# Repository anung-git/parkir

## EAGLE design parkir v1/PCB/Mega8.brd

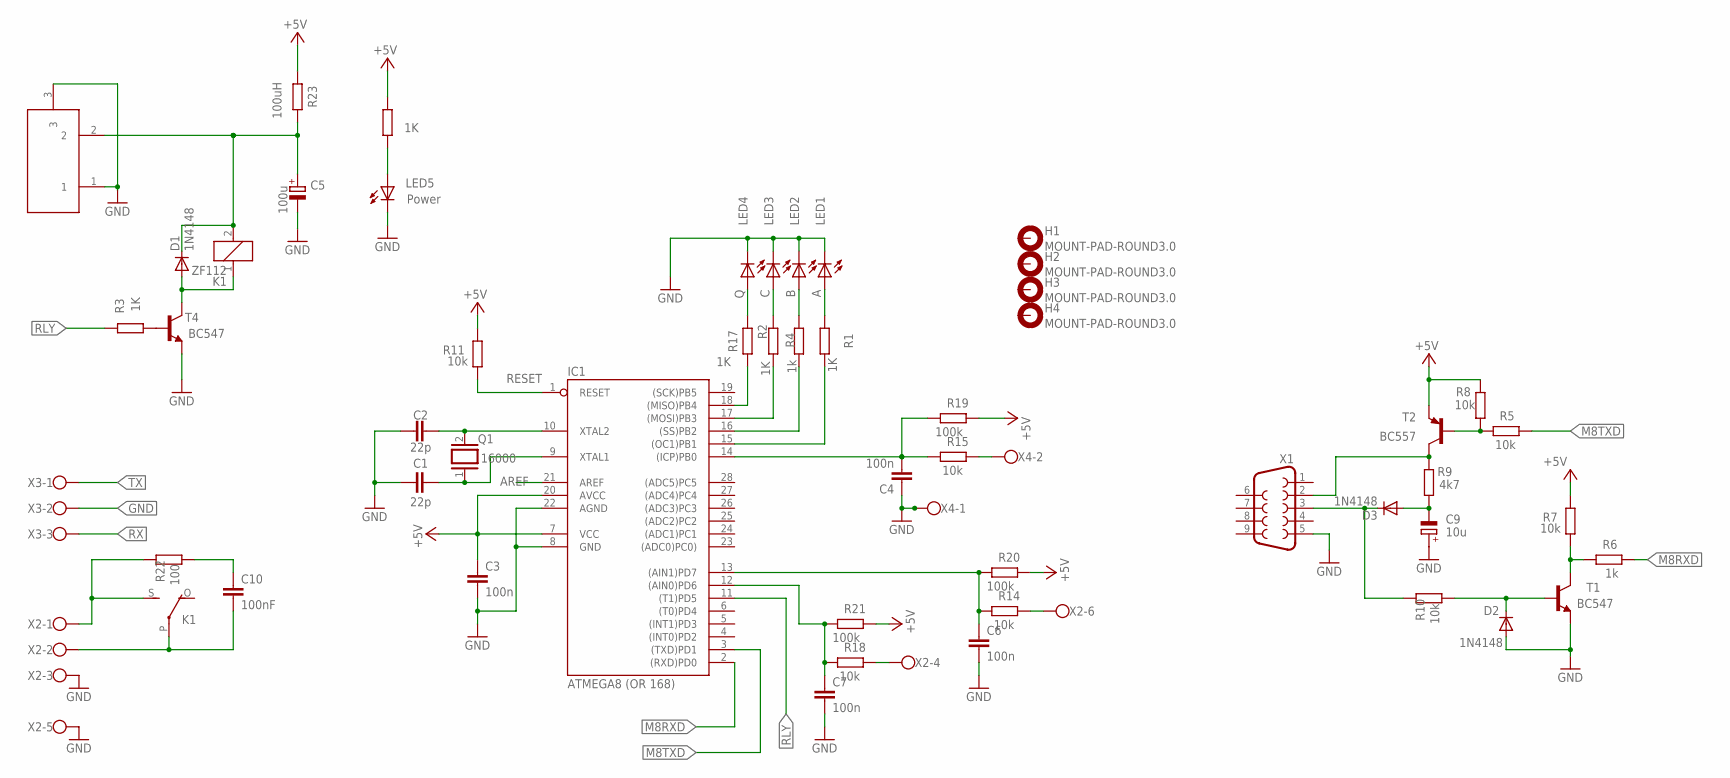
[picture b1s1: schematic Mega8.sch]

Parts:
C1, C2: 22p; C050-025X075
C3, C4, C6, C7: 100n; C050-025X075
C5: 100u; E3,5-8
C9: 10u; E5-6
C10: 100nF; C102-043X133
D1, D2, D3: 1N4148; DO35-10
DC1: DC21MMX; DC-21MM
H1, H2, H3, H4: MOUNT-PAD-ROUND3.0; 3,0-PAD
IC1: ATMEGA8 (OR 168); DIL28-3
K1: ZF112
LED1: A; LED3MM
LED2: B; LED3MM
LED3: C; LED3MM
LED4: Q; LED3MM
LED5: Power; LED3MM
Q1: 16000; Q
R1, R2, R3, R16, R17: 1K; 0207/10
R4, R6: 1k; 0207/10
R5, R7, R8, R10, R11, R14, R15, R18: 10k; 0207/10
R9: 4k7; 0207/10
R19, R20, R21: 100k; 0207/10
R22: 100; 0207/10
R23: 100uH; 0207/10
T1, T4: BC547; TO92
T2: BC557; TO92-EBC
X1: F09H
X2: W237-6
X3: W237-103
X4: W237-102

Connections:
+5V: C3.1, IC1.7 (VCC), IC1.20 (AVCC), R7.2, R8.1, R11.2, R16.2, R19.1, R20.1, R21.1, R23.2, T2.E
AREF: IC1.21 (AREF)
GND: C1.1, C2.1, C3.2, C4.1, C5.-, C6.2, C7.2, C9.+, D2.A, DC1.1, DC1.3, IC1.8 (GND), IC1.22 (AGND), LED1.K (C), LED2.K (C), LED3.K (C), LED4.K (C), LED5.K (C), T1.1 (E), T4.1 (E), X1.5, X2.3, X2.5, X3.2, X4.1
M8RXD: IC1.2 ((RXD)PD0), R6.1
M8TXD: IC1.3 ((TXD)PD1), R5.1
unnamed: R3.1, T4.2 (B)
unnamed: C9.-, D3.A, R9.1
unnamed: LED2.A, R4.1
unnamed: D1.A, K1.1, T4.3 (C)
unnamed: R18.1, X2.4
unnamed: C1.2, IC1.9 (XTAL1), Q1.1
unnamed: C2.2, IC1.10 (XTAL2), Q1.2
unnamed: K1.S, R22.2, X2.1
unnamed: C10.2, K1.P, X2.2
unnamed: C4.2, IC1.14 ((ICP)PB0), R15.2, R19.2
unnamed: C6.1, IC1.13 ((AIN1)PD7), R14.2, R20.2
unnamed: R14.1, X2.6
unnamed: IC1.15 ((OC1)PB1), R1.2
unnamed: IC1.16 ((SS)PB2), R4.2
unnamed: IC1.17 ((MOSI)PB3), R2.2
unnamed: LED5.A, R16.1
unnamed: C7.1, IC1.12 ((AIN0)PD6), R18.2, R21.2
unnamed: LED4.A, R17.1
unnamed: IC1.18 ((MISO)PB4), R17.2
unnamed: R15.1, X4.2
unnamed: R6.2, R7.1, T1.3 (C)
unnamed: R5.2, R8.2, T2.B
unnamed: C10.1, R22.1
unnamed: D2.C, R10.1, T1.2 (B)
unnamed: C5.+, D1.C, DC1.2, K1.2, R23.1
unnamed: LED3.A, R2.1
unnamed: LED1.A, R1.1
RESET: IC1.1 (RESET), R11.1
RLY: IC1.11 ((T1)PD5), R3.2
RX: D3.C, R10.2, X1.3, X3.3
TX: R9.2, T2.C, X1.2, X3.1

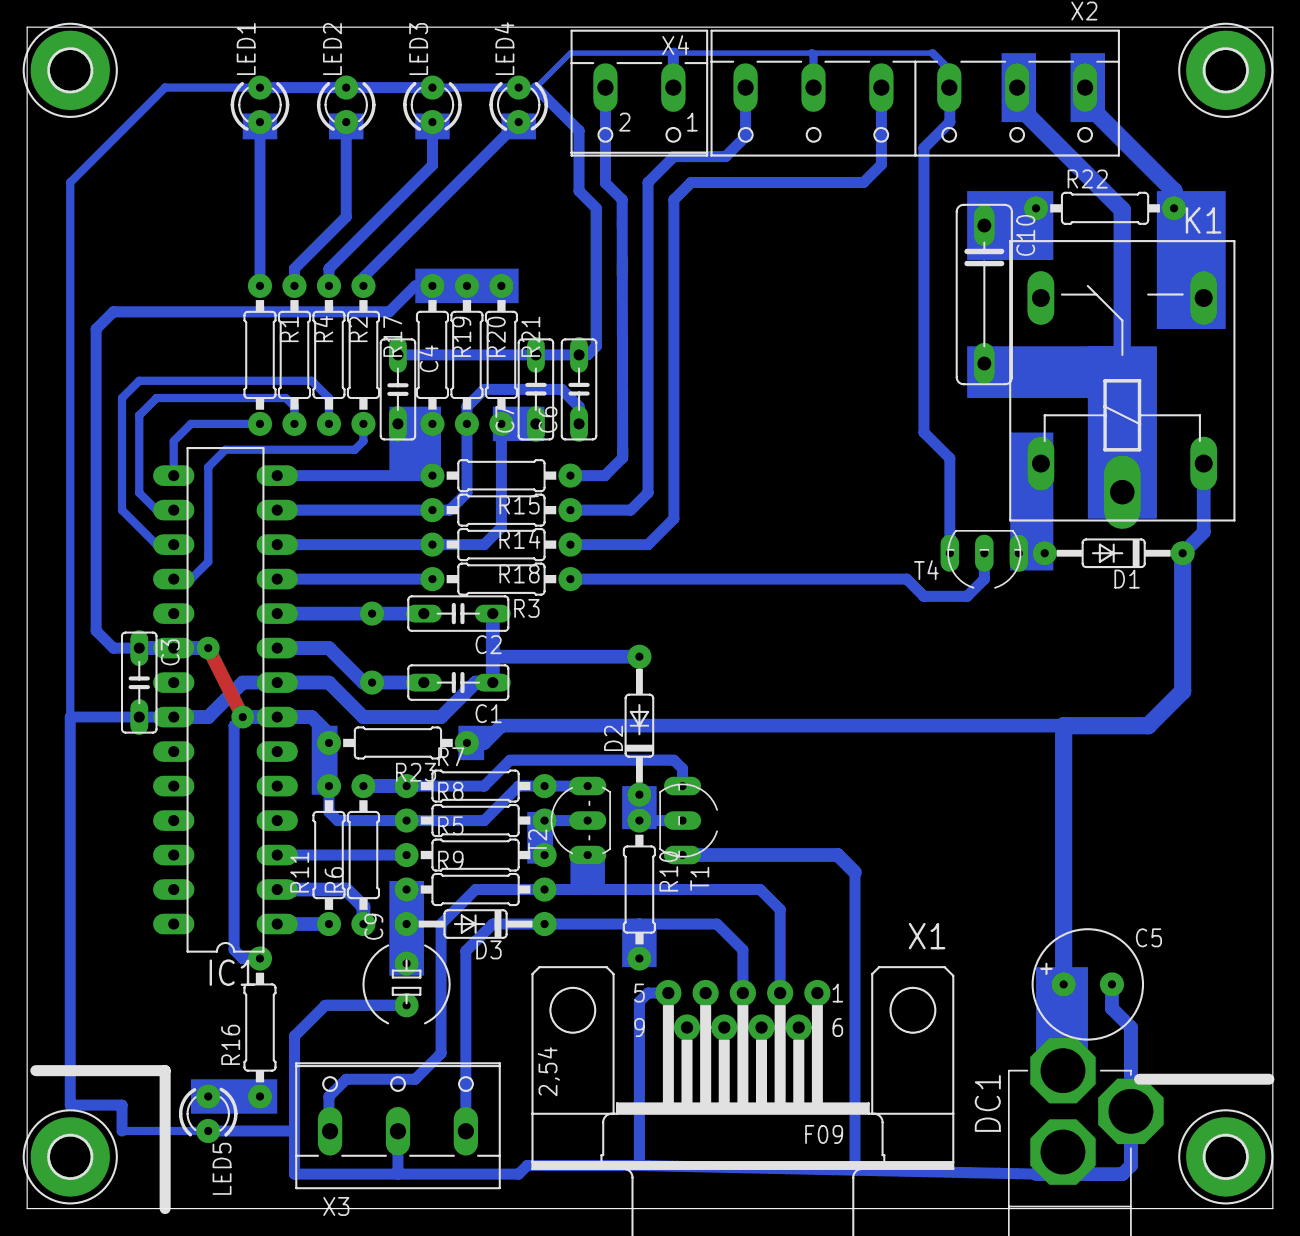
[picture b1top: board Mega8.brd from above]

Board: 2 copper layers, 91.7 x 87.0 mm, 53 parts (1 on the bottom side), 35 nets.

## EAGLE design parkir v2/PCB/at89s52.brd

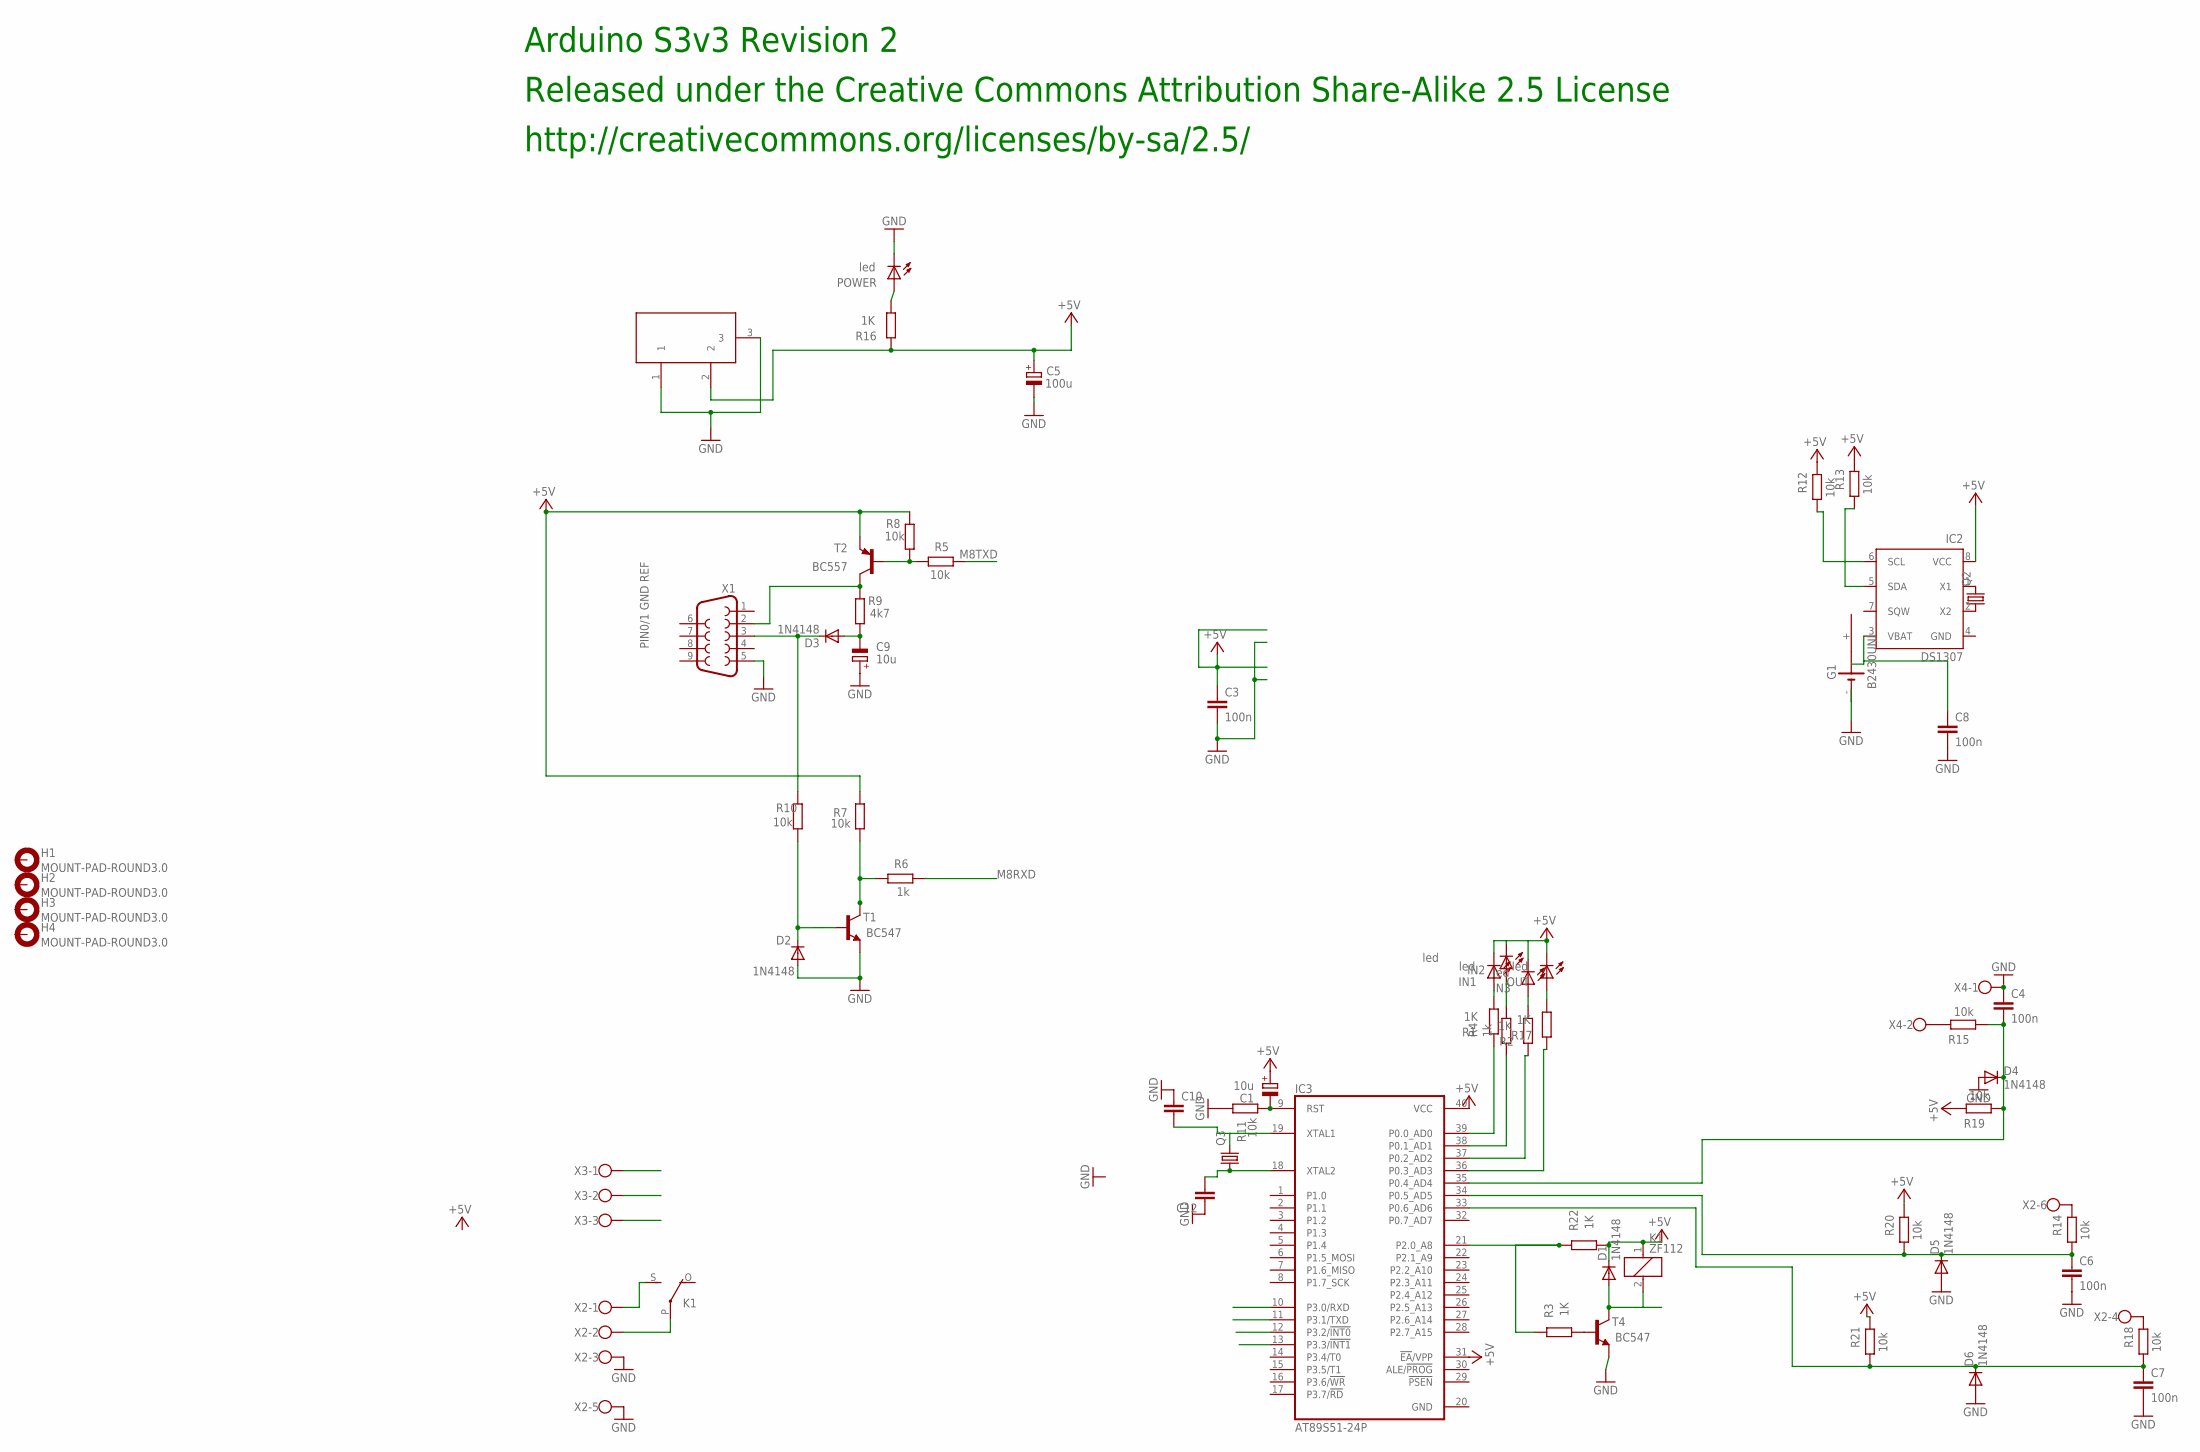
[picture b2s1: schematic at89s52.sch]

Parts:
C1, C9: 10u; E5-6
C3, C4, C6, C7, C8: 100n; C050-025X075
C5: 100u; E3,5-8
C10, C12: C-EU025-025X050; C025-025X050
D1, D2, D3, D4, D5, D6: 1N4148; DO35-10
DC1: DC21MMX; DC-21MM
G1: B2430UNI
H1, H2, H3, H4: MOUNT-PAD-ROUND3.0; 3,0-PAD
IC2: DS1307; DIL08
IC3: AT89S51-24P; DIL40
IN1, IN2, IN3: led; LED3MM
K1: ZF112
OUT: led; LED3MM
POWER: led; LED3MM
Q2: CRYSTALTC26H; TC26H
Q3: CRYSTALHC49S; HC49/S
R1, R2, R3, R16, R17, R22: 1K; 0207/10
R4, R6: 1k; 0207/10
R5, R7, R8, R10, R11, R12, R13, R14, R15, R18, R19, R20, R21: 10k; 0207/10
R9: 4k7; 0207/10
T1, T4: BC547; TO92
T2: BC557; TO92-EBC
X1: F09H
X2: W237-6
X3: W237-103
X4: W237-102

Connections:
+5V: C1.+, C3.1, C5.+, D1.C, DC1.2, IC2.8 (VCC), IC3.31 (!EA!/VPP), IC3.40 (VCC), IN1.K (C), IN2.K (C), IN3.K (C), K1.1, OUT.K (C), R7.2, R8.1, R12.1, R13.1, R16.2, R19.1, R20.1, R21.1, R22.1, T2.E
GND: C3.2, C4.1, C5.-, C6.2, C7.2, C8.2, C9.+, C10.1, C12.1, D2.A, D4.A, D5.A, D6.A, DC1.1, DC1.3, G1.-, G1.-@1 (-), IC2.4 (GND), IC3.20 (GND), POWER.K (C), R11.2, T1.1 (E), T4.1 (E), X1.5, X2.3, X2.5, X3.2, X4.1
M8RXD: IC3.10 (P3.0/RXD), R6.1
M8TXD: IC3.11 (P3.1/TXD), R5.1
unnamed: R3.1, T4.2 (B)
unnamed: C9.-, D3.A, R9.1
unnamed: IN2.A, R4.1
unnamed: D1.A, K1.2, T4.3 (C)
unnamed: R18.1, X2.4
unnamed: C12.2, IC3.18 (XTAL2), Q3.1
unnamed: C10.2, IC3.19 (XTAL1), Q3.2
unnamed: K1.S, X2.1
unnamed: K1.P, X2.2
unnamed: C8.1, G1.+@4 (+), IC2.3 (VBAT)
unnamed: C4.2, D4.C, IC3.35 (P0.4_AD4), R15.2, R19.2
unnamed: C6.1, D5.C, IC3.34 (P0.5_AD5), R14.2, R20.2
unnamed: R14.1, X2.6
unnamed: IC3.39 (P0.0_AD0), R1.2
unnamed: IC3.38 (P0.1_AD1), R4.2
unnamed: IC3.37 (P0.2_AD2), R2.2
unnamed: POWER.A, R16.1
unnamed: C7.1, D6.C, IC3.33 (P0.6_AD6), R18.2, R21.2
unnamed: OUT.A, R17.1
unnamed: IC3.36 (P0.3_AD3), R17.2
unnamed: R15.1, X4.2
unnamed: IC2.1 (X1), Q2.2
unnamed: IC2.2 (X2), Q2.1
unnamed: R6.2, R7.1, T1.3 (C)
unnamed: R5.2, R8.2, T2.B
unnamed: C1.-, IC3.9 (RST), R11.1
unnamed: D2.C, R10.1, T1.2 (B)
unnamed: IN3.A, R2.1
unnamed: IN1.A, R1.1
RLY: IC3.21 (P2.0_A8), R3.2, R22.2
RX: D3.C, R10.2, X1.3, X3.3
SCL: IC2.6 (SCL), IC3.13 (P3.3/!INT1), R12.2
SDA: IC2.5 (SDA), IC3.12 (P3.2/!INT0), R13.2
TX: R9.2, T2.C, X1.2, X3.1

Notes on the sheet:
PIN0/1 GND REF
Released under the Creative Commons Attribution Share-Alike 2.5 License
http://creativecommons.org/licenses/by-sa/2.5/
Arduino S3v3 Revision 2

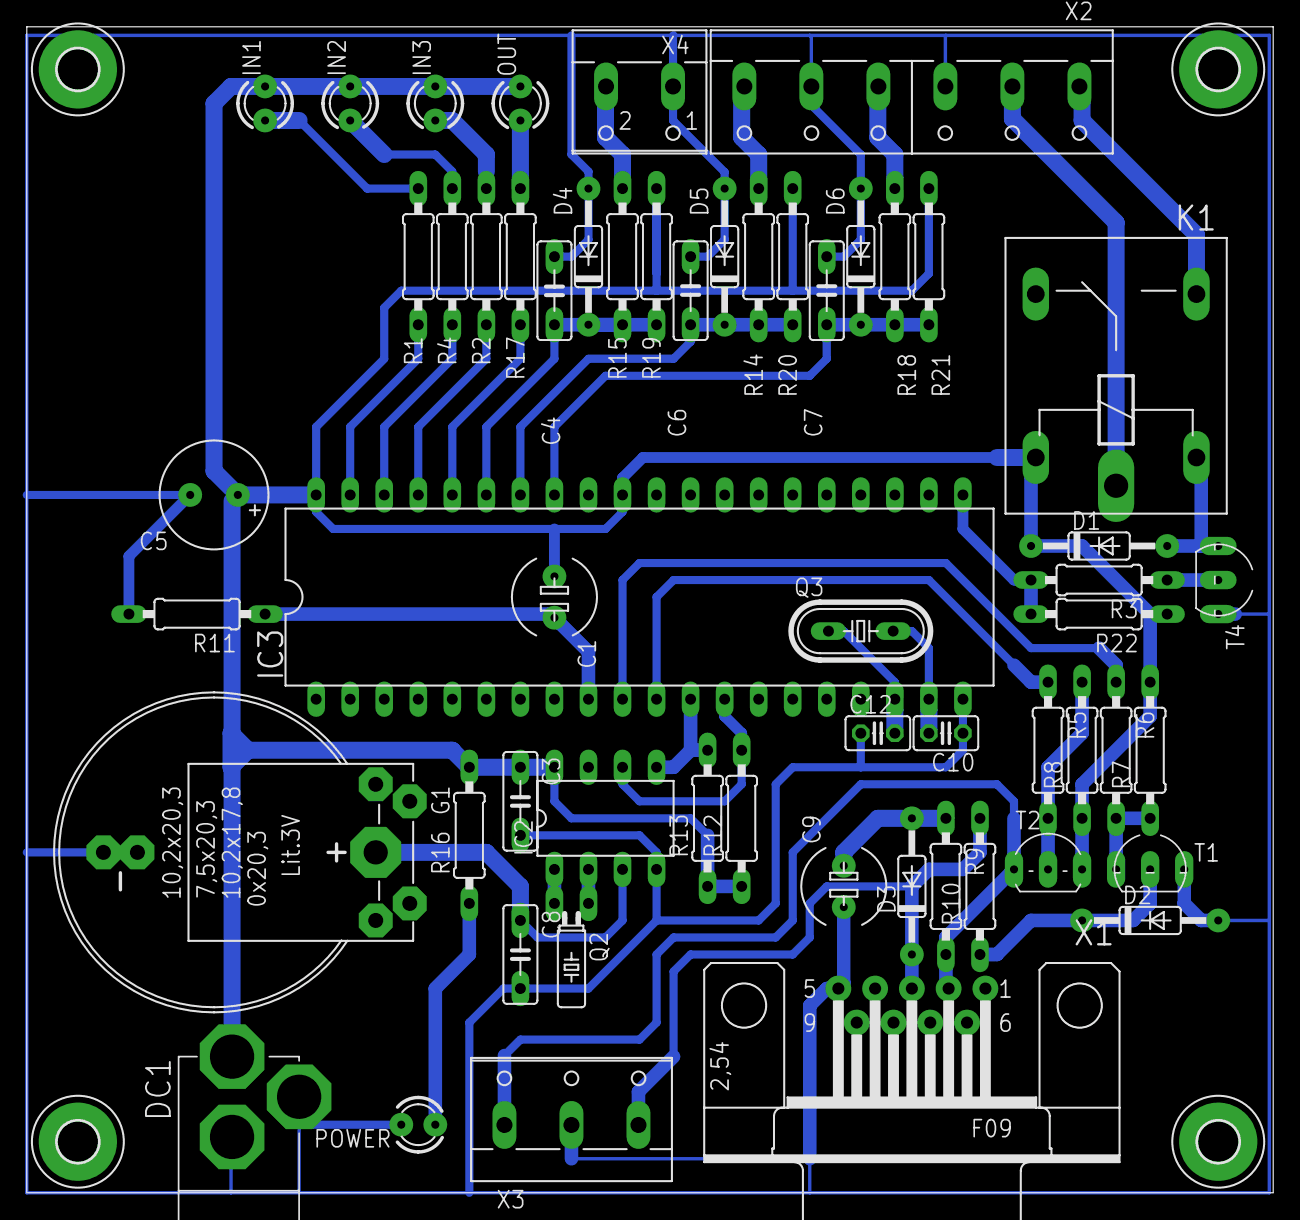
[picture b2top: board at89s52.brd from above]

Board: 2 copper layers, 93.0 x 87.0 mm, 61 parts (0 on the bottom side), 38 nets.

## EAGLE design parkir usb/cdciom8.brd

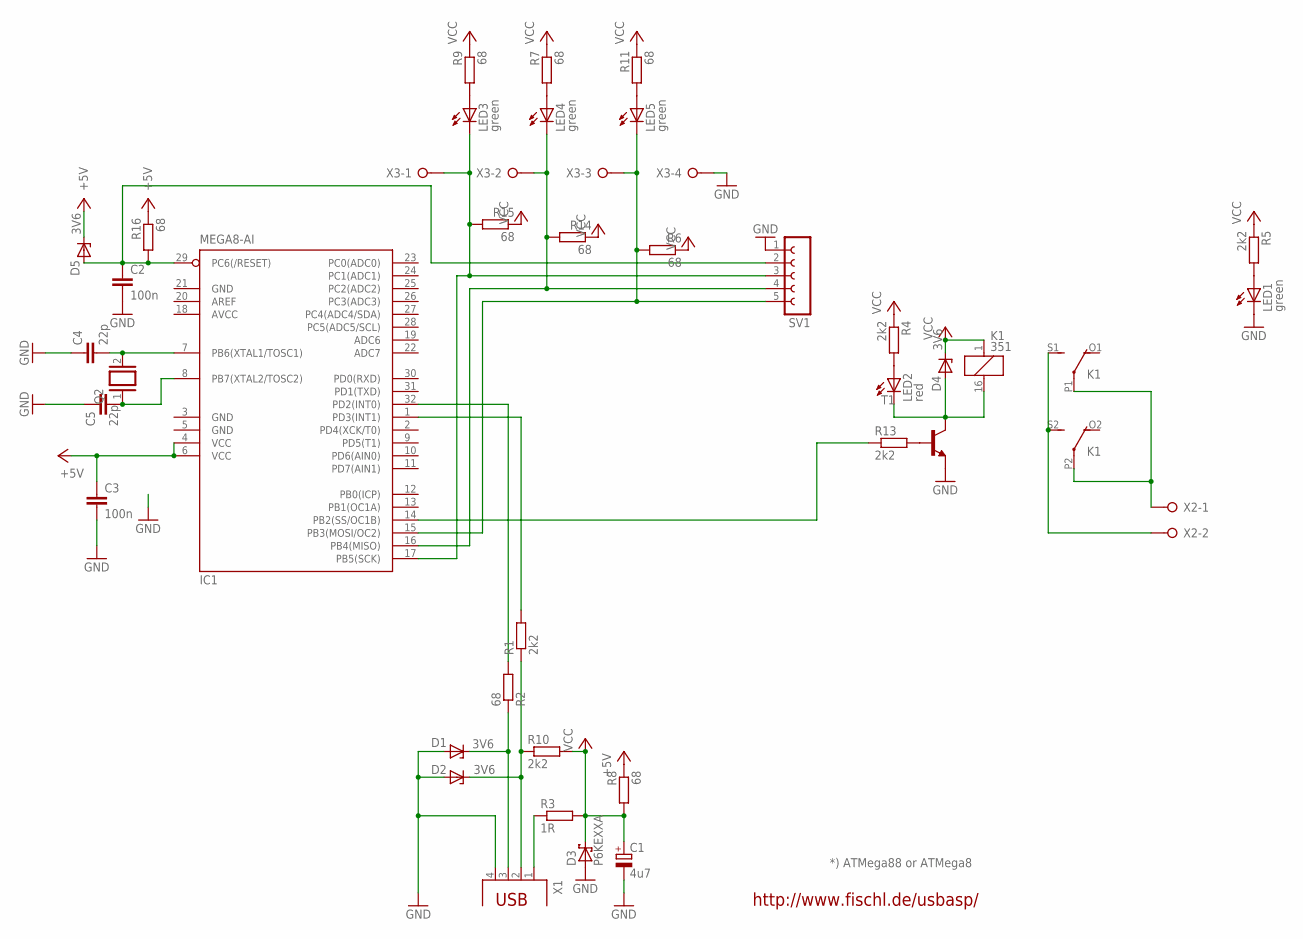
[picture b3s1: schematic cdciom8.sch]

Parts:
C1: 4u7; E2,5-5
C2, C3: 100n; C025-024X044
C4, C5: 22p; C025-024X044
D1, D2, D4, D5: 3V6; DO34Z7
D3: P6KEXXA; C1702-15
IC1: MEGA8-AI; TQFP32-08
K1: 351
LED1, LED3, LED4, LED5: green; LED3MM
LED2: red; LED3MM
Q2: XTAL/S; QS
R1, R4, R5, R10, R13: 2k2; 0207/2V
R2, R6, R7, R8, R9, R11, R14, R15, R16: 68; 0207/10
R3: 1R; 0207/2V
SV1: FE05-1
T1: 2N4124-NPN-TO92-CBE; TO92-CBE
X1: PN61729
X2: W237-02P; W237-132
X3: W237-04P; W237-4P

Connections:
+5V: C3.1, D5.C, IC1.4 (VCC), IC1.6 (VCC), R8.1, R16.1
AVCC: IC1.18 (AVCC)
GND: C1.-, C2.2, C3.2, C4.1, C5.1, D1.A, D2.A, D3.A, IC1.3 (GND), IC1.5 (GND), IC1.21 (GND), LED1.K (C), SV1.1, T1.E, X1.4, X3.4
unnamed: C2.1, D5.A, IC1.29 (PC6(/RESET)), R16.2, SV1.2
unnamed: R13.2, T1.B
unnamed: IC1.14 (PB2(SS/OC1B)), R13.1
unnamed: D4.A, K1.16 (2), LED2.K (C), T1.C
unnamed: D2.C, R1.1, R10.1, X1.2
unnamed: K1.S1 (S), K1.S2 (S), X2.2
unnamed: IC1.32 (PD2(INT0)), R2.2
unnamed: D1.C, R2.1, X1.3
unnamed: LED2.A, R4.2
unnamed: K1.P1, K1.P2, X2.1
unnamed: R3.1, X1.1
unnamed: LED1.A, R5.2
unnamed: LED3.A, R9.2
unnamed: LED4.A, R7.2
unnamed: LED5.A, R11.2
unnamed: IC1.1 (PD3(INT1)), R1.2
unnamed: IC1.17 (PB5(SCK)), LED3.K (C), R15.2, SV1.3, X3.1
unnamed: IC1.16 (PB4(MISO)), LED4.K (C), R14.2, SV1.4, X3.2
unnamed: IC1.15 (PB3(MOSI/OC2)), LED5.K (C), R6.2, SV1.5, X3.3
unnamed: C4.2, IC1.7 (PB6(XTAL1/TOSC1)), Q2.2
unnamed: C5.2, IC1.8 (PB7(XTAL2/TOSC2)), Q2.1
VCC: C1.+, D3.C, D4.C, K1.1, R3.2, R4.1, R5.1, R6.1, R7.1, R8.2, R9.1, R10.2, R11.1, R14.1, R15.1

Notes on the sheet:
http://www.fischl.de/usbasp/
*) ATMega88 or ATMega8

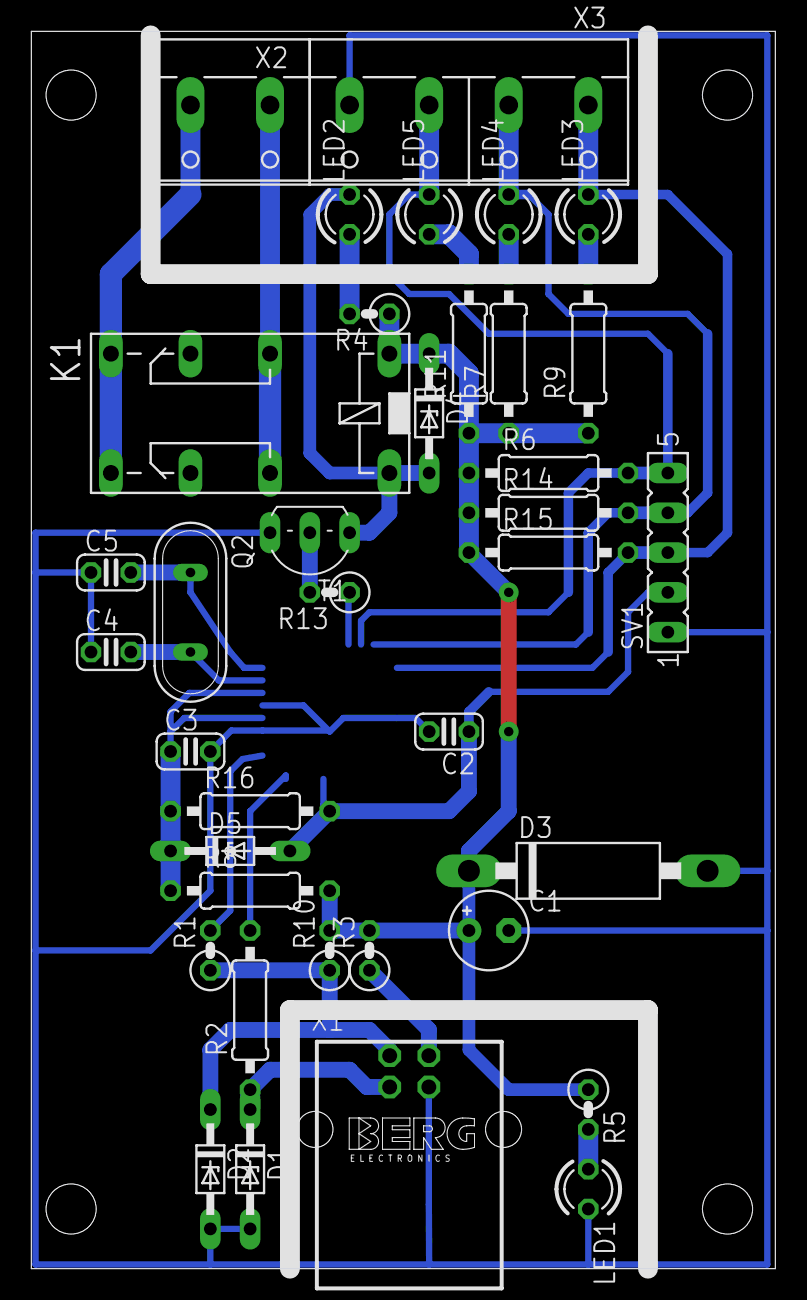
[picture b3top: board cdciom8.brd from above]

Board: 2 copper layers, 47.5 x 79.0 mm, 38 parts (1 on the bottom side), 24 nets.

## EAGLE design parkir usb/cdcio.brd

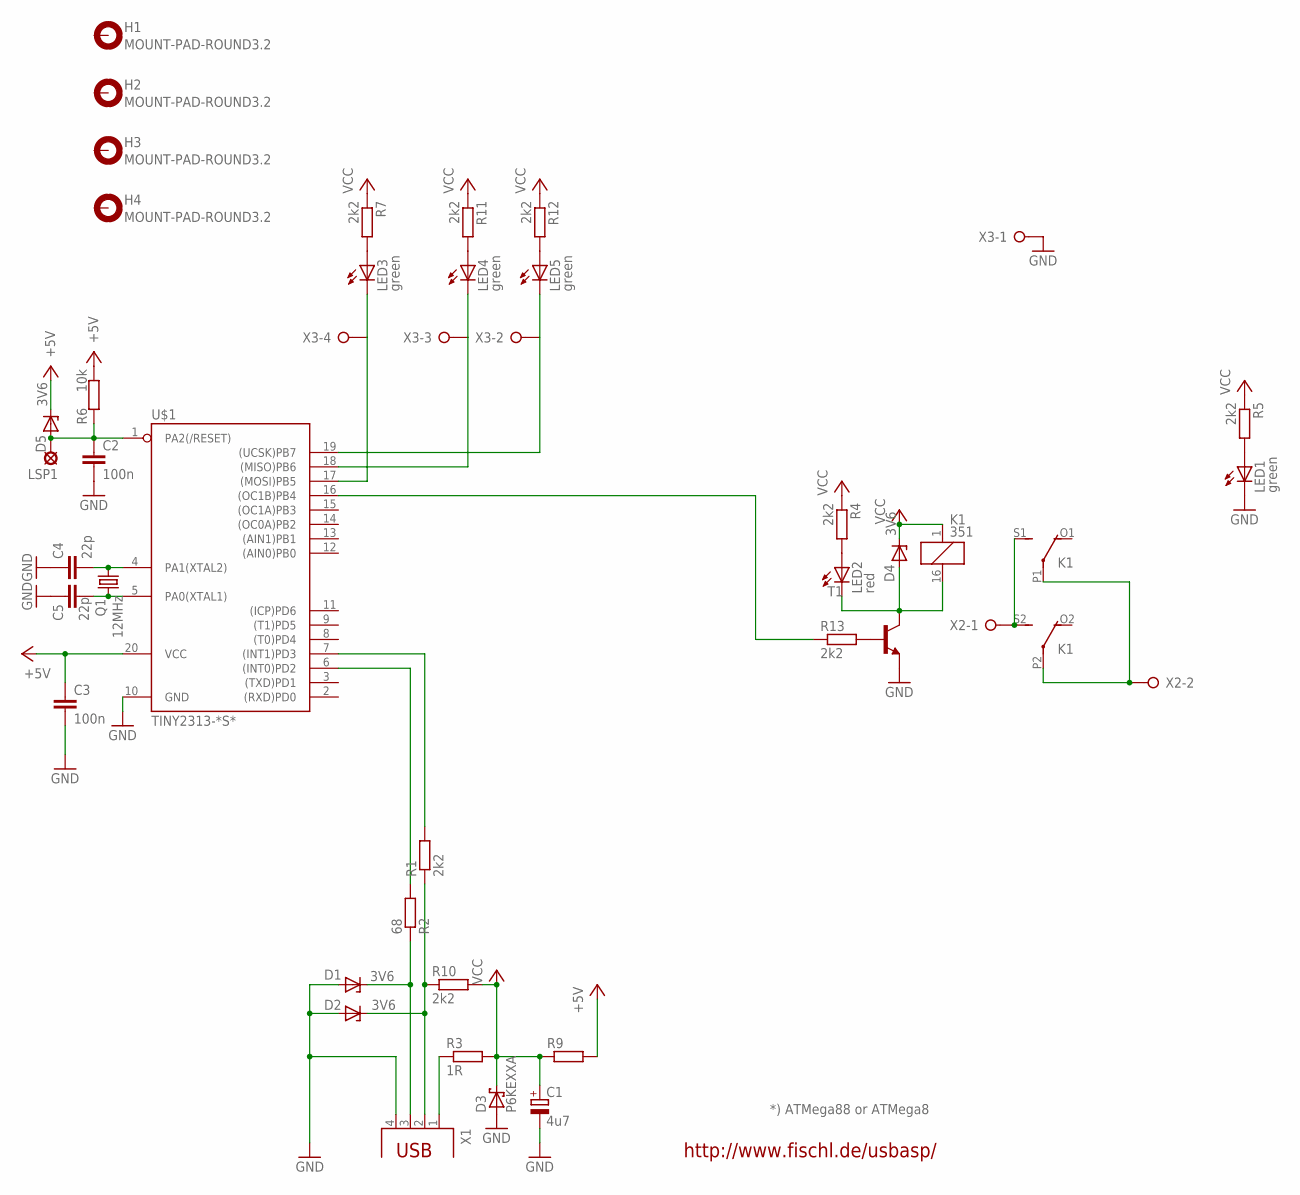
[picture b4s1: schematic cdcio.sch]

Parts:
C1: 4u7; E2,5-5
C2, C3: 100n; C025-024X044
C4, C5: 22p; C025-024X044
D1, D2, D4, D5: 3V6; DO34Z7
D3: P6KEXXA; C1702-15
H1, H2, H3, H4: MOUNT-PAD-ROUND3.2; 3,2-PAD
K1: 351
LED1, LED3, LED4, LED5: green; LED3MM
LED2: red; LED3MM
LSP1: LSP10
Q1: 12MHz; HC49/S
R1, R4, R5, R7, R10, R11, R12, R13: 2k2; 0207/2V
R2: 68; 0207/10
R3: 1R; 0207/2V
R6: 10k; 0207/10
R9: R-EU_0207/2V; 0207/2V
T1: 2N4124-NPN-TO92-CBE; TO92-CBE
U$1: TINY2313-*S*; SO20L$
X1: PN61729
X2: W237-02P; W237-132
X3: W237-04P; W237-4P

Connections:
+5V: C3.1, D5.C, R6.1, R9.2, U$1.20 (VCC)
GND: C1.-, C2.2, C3.2, C4.1, C5.1, D1.A, D2.A, D3.A, LED1.K (C), T1.E, U$1.10 (GND), X1.4, X3.1
unnamed: C2.1, D5.A, LSP1.MP, R6.2, U$1.1 (PA2(/RESET))
unnamed: R13.2, T1.B
unnamed: R13.1, U$1.16 ((OC1B)PB4)
unnamed: D4.A, K1.16 (2), LED2.K (C), T1.C
unnamed: D2.C, R1.1, R10.1, X1.2
unnamed: K1.S1 (S), K1.S2 (S), X2.1
unnamed: R2.2, U$1.6 ((INT0)PD2)
unnamed: D1.C, R2.1, X1.3
unnamed: LED2.A, R4.2
unnamed: K1.P1, K1.P2, X2.2
unnamed: R3.1, X1.1
unnamed: LED1.A, R5.2
unnamed: LED3.A, R7.2
unnamed: LED4.A, R11.2
unnamed: LED5.A, R12.2
unnamed: R1.2, U$1.7 ((INT1)PD3)
unnamed: LED3.K (C), U$1.17 ((MOSI)PB5), X3.4
unnamed: LED4.K (C), U$1.18 ((MISO)PB6), X3.3
unnamed: LED5.K (C), U$1.19 ((UCSK)PB7), X3.2
unnamed: C4.2, Q1.2, U$1.4 (PA1(XTAL2))
unnamed: C5.2, Q1.1, U$1.5 (PA0(XTAL1))
VCC: C1.+, D3.C, D4.C, K1.1, R3.2, R4.1, R5.1, R7.1, R9.1, R10.2, R11.1, R12.1

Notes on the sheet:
http://www.fischl.de/usbasp/
*) ATMega88 or ATMega8

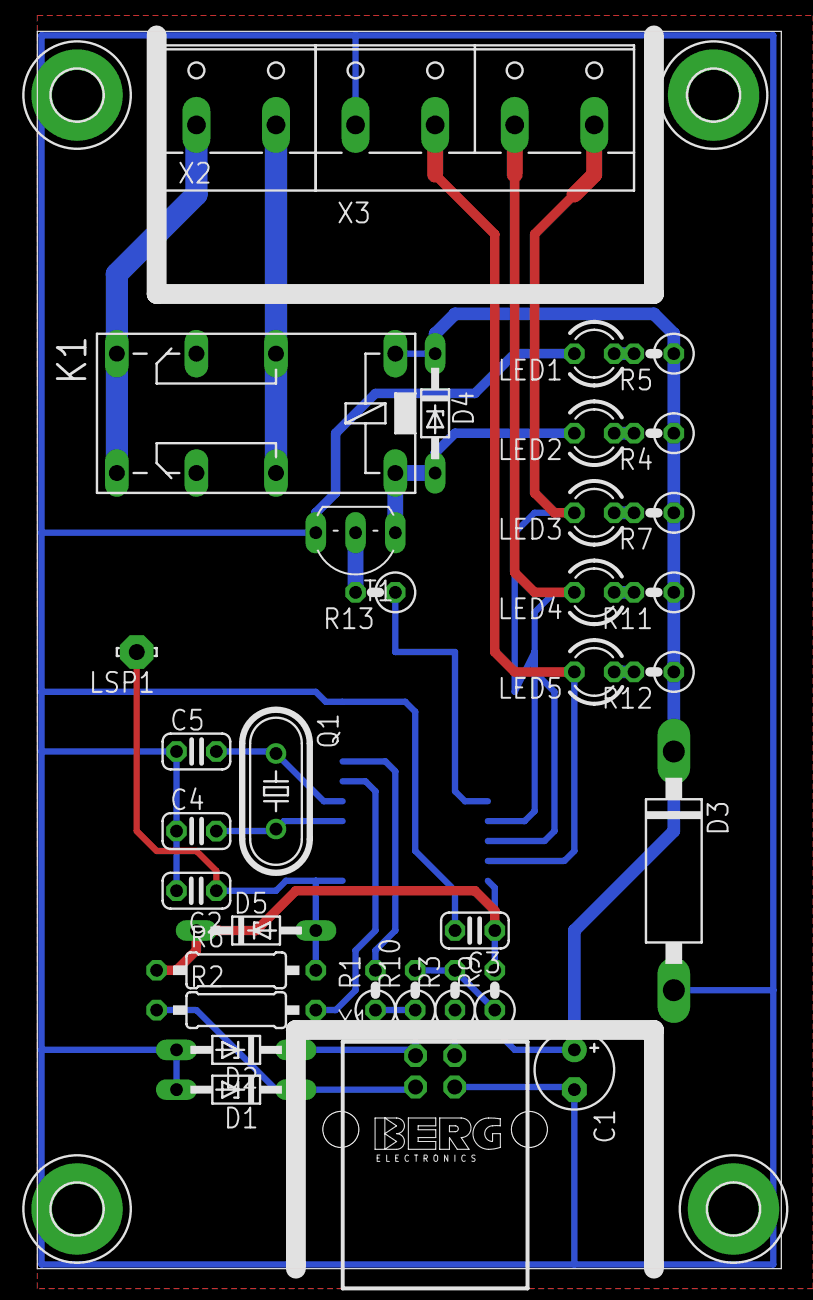
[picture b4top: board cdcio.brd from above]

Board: 2 copper layers, 47.5 x 79.0 mm, 39 parts (1 on the bottom side), 24 nets.

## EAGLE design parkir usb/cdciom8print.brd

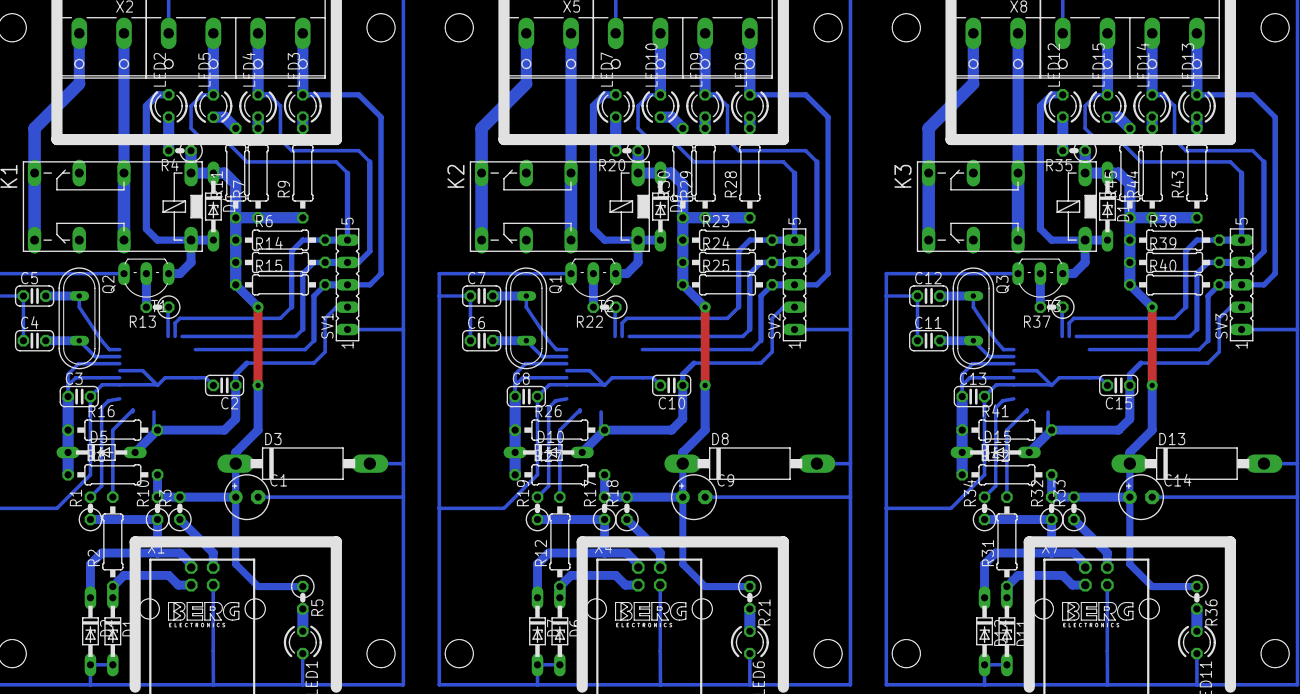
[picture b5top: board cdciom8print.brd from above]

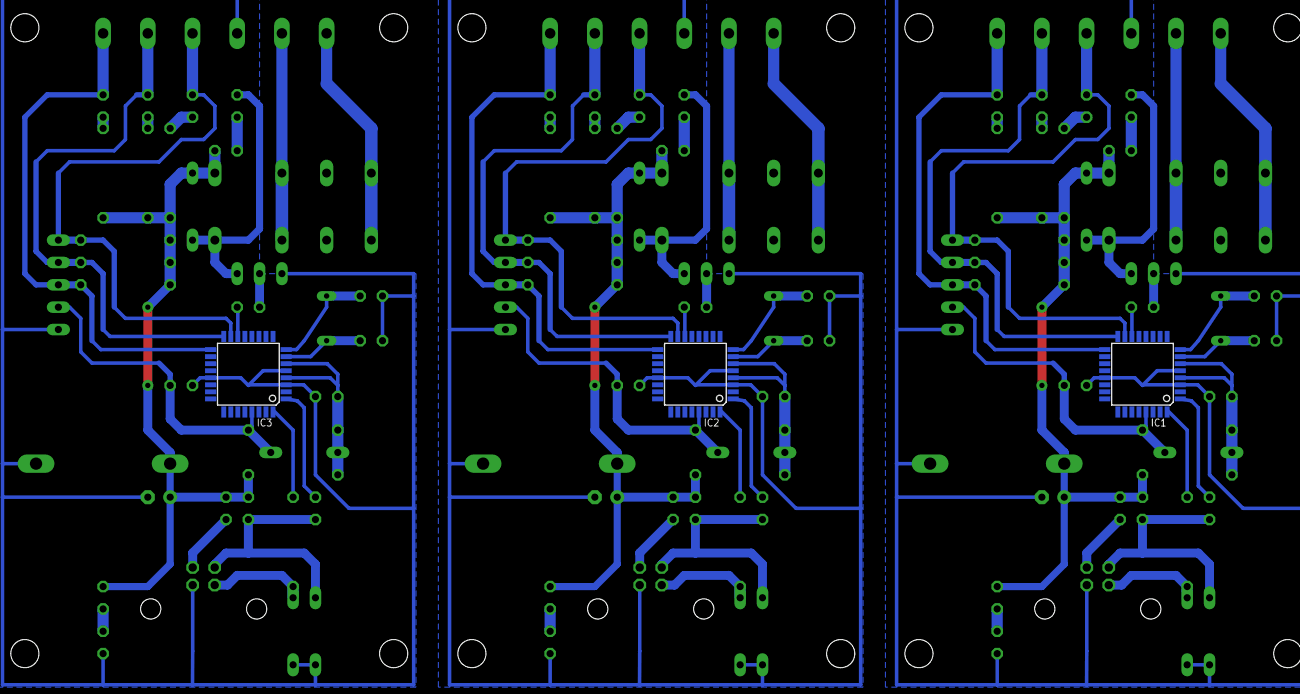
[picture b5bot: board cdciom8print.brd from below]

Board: 2 copper layers, 114 parts (3 on the bottom side), 72 nets.

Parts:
C1, C9, C14: 4u7; E2,5-5
C2, C3, C8, C10, C13, C15: 100n; C025-024X044
C4, C5, C6, C7, C11, C12: 22p; C025-024X044
D1, D2, D4, D5, D6, D7, D9, D10, D11, D12, D14, D15: 3V6; DO34Z7
D3, D8, D13: P6KEXXA; C1702-15
IC1, IC2, IC3: MEGA8-AI; TQFP32-08
K1, K2, K3: 351
LED1, LED3, LED4, LED5, LED6, LED8, LED9, LED10, LED11, LED13, LED14, LED15: green; LED3MM
LED2, LED7, LED12: red; LED3MM
Q1, Q2, Q3: QS
R1, R4, R5, R10, R13, R17, R19, R20, R21, R22, R32, R34, R35, R36, R37: 2k2; 0207/2V
R2, R6, R7, R8, R9, R11, R12, R14, R15, R16, R23, R24, R25, R26, R27, R28, R29, R30, R31, R38, R39, R40, R41, R42, R43, R44, R45: 68; 0207/10
R3, R18, R33: 1R; 0207/2V
SV1, SV2, SV3: FE05-1
T1, T2, T3: TO92-CBE
X1, X4, X7: PN61729
X2, X5, X8: W237-132
X3, X6, X9: W237-4P

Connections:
+5V: C3.1, D5.C, IC1.4, IC1.6, R8.1, R16.1
+5V1: C8.1, D10.C, IC2.4, IC2.6, R26.1, R27.1
+5V2: C13.1, D15.C, IC3.4, IC3.6, R41.1, R42.1
GND: C1.-, C2.2, C3.2, C4.1, C5.1, D1.A, D2.A, D3.A, IC1.3, IC1.5, IC1.21, LED1.K, SV1.1, T1.E, X1.4, X3.4
GND1: C6.1, C7.1, C8.2, C9.-, C10.2, D6.A, D7.A, D8.A, IC2.3, IC2.5, IC2.21, LED6.K, SV2.1, T2.E, X4.4, X6.4
GND2: C11.1, C12.1, C13.2, C14.-, C15.2, D11.A, D12.A, D13.A, IC3.3, IC3.5, IC3.21, LED11.K, SV3.1, T3.E, X7.4, X9.4
unnamed: C2.1, D5.A, IC1.29, R16.2, SV1.2
unnamed: R13.2, T1.B
unnamed: IC1.14, R13.1
unnamed: D4.A, K1.16, LED2.K, T1.C
unnamed: D2.C, R1.1, R10.1, X1.2
unnamed: K1.S1, K1.S2, X2.2
unnamed: IC1.32, R2.2
unnamed: D1.C, R2.1, X1.3
unnamed: LED2.A, R4.2
unnamed: K1.P1, K1.P2, X2.1
unnamed: R3.1, X1.1
unnamed: LED1.A, R5.2
unnamed: LED3.A, R9.2
unnamed: LED4.A, R7.2
unnamed: LED5.A, R11.2
unnamed: IC1.1, R1.2
unnamed: IC1.17, LED3.K, R15.2, SV1.3, X3.1
unnamed: IC1.16, LED4.K, R14.2, SV1.4, X3.2
unnamed: IC1.15, LED5.K, R6.2, SV1.5, X3.3
unnamed: D7.C, R17.1, R19.1, X4.2
unnamed: D6.C, R12.1, X4.3
unnamed: C4.2, IC1.7, Q2.2
unnamed: C5.2, IC1.8, Q2.1
unnamed: C6.2, IC2.7, Q1.2
unnamed: C7.2, IC2.8, Q1.1
unnamed: IC2.32, R12.2
unnamed: C10.1, D10.A, IC2.29, R26.2, SV2.2
unnamed: IC2.1, R19.2
unnamed: D9.A, K2.16, LED7.K, T2.C
unnamed: K2.S1, K2.S2, X5.2
unnamed: K2.P1, K2.P2, X5.1
unnamed: R18.1, X4.1
unnamed: LED7.A, R20.2
unnamed: LED6.A, R21.2
unnamed: LED9.A, R29.2
unnamed: LED10.A, R30.2
unnamed: R22.2, T2.B
unnamed: IC2.17, LED8.K, R25.2, SV2.3, X6.1
unnamed: IC2.16, LED9.K, R24.2, SV2.4, X6.2
unnamed: IC2.15, LED10.K, R23.2, SV2.5, X6.3
unnamed: IC2.14, R22.1
unnamed: LED8.A, R28.2
unnamed: D12.C, R32.1, R34.1, X7.2
unnamed: D11.C, R31.1, X7.3
unnamed: C11.2, IC3.7, Q3.2
unnamed: C12.2, IC3.8, Q3.1
unnamed: IC3.32, R31.2
unnamed: C15.1, D15.A, IC3.29, R41.2, SV3.2
unnamed: IC3.1, R34.2
unnamed: D14.A, K3.16, LED12.K, T3.C
unnamed: K3.S1, K3.S2, X8.2
unnamed: K3.P1, K3.P2, X8.1
unnamed: R33.1, X7.1
unnamed: LED12.A, R35.2
unnamed: LED11.A, R36.2
unnamed: LED14.A, R44.2
unnamed: LED15.A, R45.2
unnamed: R37.2, T3.B
unnamed: IC3.17, LED13.K, R40.2, SV3.3, X9.1
unnamed: IC3.16, LED14.K, R39.2, SV3.4, X9.2
unnamed: IC3.15, LED15.K, R38.2, SV3.5, X9.3
unnamed: IC3.14, R37.1
unnamed: LED13.A, R43.2
VCC: C1.+, D3.C, D4.C, K1.1, R3.2, R4.1, R5.1, R6.1, R7.1, R8.2, R9.1, R10.2, R11.1, R14.1, R15.1
VCC1: C9.+, D8.C, D9.C, K2.1, R17.2, R18.2, R20.1, R21.1, R23.1, R24.1, R25.1, R27.2, R28.1, R29.1, R30.1
VCC2: C14.+, D13.C, D14.C, K3.1, R32.2, R33.2, R35.1, R36.1, R38.1, R39.1, R40.1, R42.2, R43.1, R44.1, R45.1

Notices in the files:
parkir usb/femware/cdcio.2009-07-15/mega48/main.c:
Copyright: (c) 2007 by Recursion Co., Ltd.
License: Proprietary, free under certain conditions. See Documentation.
